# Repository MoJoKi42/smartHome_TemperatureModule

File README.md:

# smartHome_TemperatureModule
Temperature module for my smart home project based on a **ATmega324PB**. It can be powered by one/two 18650 BatteryCell or USB-C. If you use the battery, there is also a small PV charging circuit that makes battery replacement unnecessary.
Data communication works over the **433 Mhz band** with the RFM69 module soldered to the board.

Measurements can be taken every 8 seconds (or multiples thereof). There are also two sensor options on board. One option is the **SHT41** I2C digital temperature and humidity sensor from Sensirion. The other option is a standard 100R **NTC resistor** (in my case 44001RC) powered by a constant current source. The measurement is done with a differential ADC.

*keep in mind*: The firmware is still under development. Some changes need to be made to the data header for transmission.

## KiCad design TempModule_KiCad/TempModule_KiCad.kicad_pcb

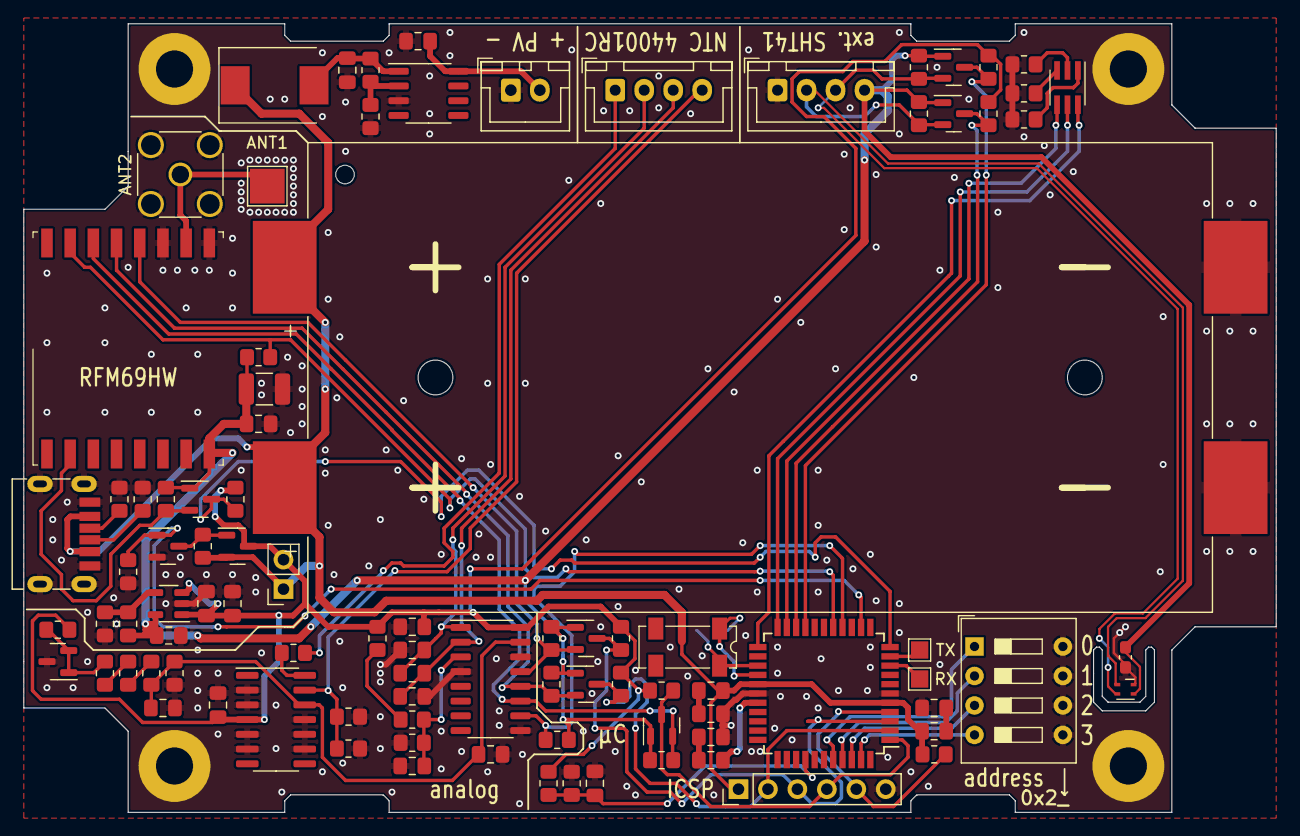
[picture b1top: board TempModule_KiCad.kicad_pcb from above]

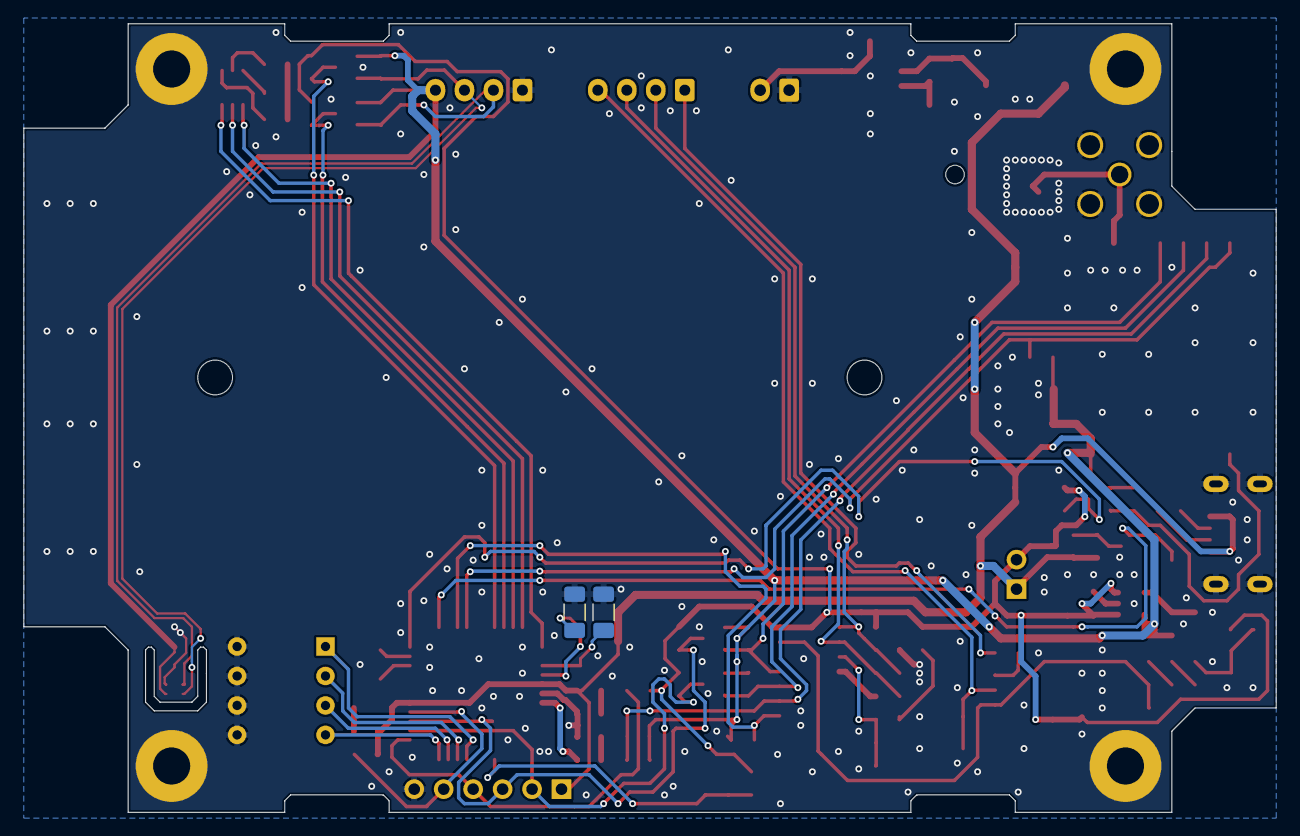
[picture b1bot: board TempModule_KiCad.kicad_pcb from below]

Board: 2 copper layers, 108.0 x 68.0 mm, 99 parts (2 on the bottom side), 58 nets.

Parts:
ANT1: ext. cable ANT; TestPoint_Pad_3.0x3.0mm
ANT2: SMA_connector; SMA_Wurth_60312002114503_Vertical
BATT1: 18650_SMD_Holder_2x
C1, C3, C5, C7, C8, C11, C12, C13, C15, C16, C17, C22, C23: 100n; C_0805_2012Metric_Pad1.18x1.45mm_HandSolder
C2: 10µ 16V; C_1210_3225Metric_Pad1.33x2.70mm_HandSolder
C4, C6: 2.2µ; C_0805_2012Metric_Pad1.18x1.45mm_HandSolder
C9, C14, C18, C19, C20, C21: 330n; C_0805_2012Metric_Pad1.18x1.45mm_HandSolder
C10: 100n; C_0603_1608Metric_Pad1.08x0.95mm_HandSolder
C24, C25: 15pF 1206; C_1206_3216Metric_Pad1.33x1.80mm_HandSolder
D1: VS-30BQ060; D_SMC
D2: ASMT-YTB2-0BB02; LED_Avago_PLCC6_3x2.8mm
J2: always_on_jumper; PinSocket_1x02_P2.54mm_Vertical
J3: 44001RC NTC; JST_XH_B4B-XH-A_1x04_P2.50mm_Vertical
J4: ICSP; PinHeader_1x06_P2.54mm_Vertical
J5: ext. SHT41; JST_XH_B4B-XH-A_1x04_P2.50mm_Vertical
J6: PV_Panel; JST_XH_B2B-XH-A_1x02_P2.50mm_Vertical
Q1: FDN306P; SOT-23
Q2: BSS138P; SOT-23
Q3, Q4, Q5, Q6, Q7, Q8: BSS138; SOT-23
R1, R4: 100k; R_0805_2012Metric_Pad1.20x1.40mm_HandSolder
R2, R8: 200R; R_0805_2012Metric_Pad1.20x1.40mm_HandSolder
R3, R5, R9, R10, R11, R12: 1k 0.5%; R_0805_2012Metric_Pad1.20x1.40mm_HandSolder
R6: 6.2k; R_0805_2012Metric_Pad1.20x1.40mm_HandSolder
R7, R16, R18, R19, R25, R26, R27, R28, R29, R30, R31, R32, R33, R34, R35, R36, R39: 10k; R_0805_2012Metric_Pad1.20x1.40mm_HandSolder
R13: 2k2; R_0805_2012Metric_Pad1.20x1.40mm_HandSolder
R14: 6k8; R_0805_2012Metric_Pad1.20x1.40mm_HandSolder
R15: 1k; R_0805_2012Metric_Pad1.20x1.40mm_HandSolder
R17: 47k; R_0805_2012Metric_Pad1.20x1.40mm_HandSolder
R20: 30k; R_0805_2012Metric_Pad1.20x1.40mm_HandSolder
R21: 7.5k; R_0805_2012Metric_Pad1.20x1.40mm_HandSolder
R22, R23, R24: 680R; R_0805_2012Metric_Pad1.20x1.40mm_HandSolder
R37, R38: 5.1k; R_0805_2012Metric_Pad1.20x1.40mm_HandSolder
SW1: SW_DIP_x04; SW_DIP_SPSTx04_Slide_9.78x12.34mm_W7.62mm_P2.54mm
TP2: TX; TestPoint_Pad_1.5x1.5mm
TP3: RX; TestPoint_Pad_1.5x1.5mm
U1: MCP6004; SO-14_3.9x8.65mm_P1.27mm
U2: RFM69HW; HOPERF_RFM69HW
U3: AP2210-ADJ; SOT-23-5
U4: TL432DBZ; SOT-23
U5: SHT41-AD1F-R2; Sensirion_DFN-4_1.5x1.5mm_P0.8mm_SHT4x_NoCentralPad
U6: LT1121CS8; SO-8_3.9x4.9mm_P1.27mm
U7: MCP3304; SO-16_3.9x9.9mm_P1.27mm
U8: ATmega324PB-A; TQFP-44_10x10mm_P0.8mm
U9: USB-C_6Pin_C2689837
U10, U11, U12, U13: Screw; Via_ScrewHole_3mm
Y1: Crystal_32.768_kHz; Crystal_SMD_SeikoEpson_MC306-4Pin_8.0x3.2mm

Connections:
+3.3V: C1.2, C2.1, C6.1, C10.2, J5.4, Q3.1 (G), Q4.1 (G), Q5.1 (G), Q6.1 (G), Q7.1 (G), Q8.1 (G), R6.1, R18.2, R19.2, R25.1, R27.1, R29.1, R31.1, R33.1, R35.1, U2.8 (3.3V), U3.5 (VOUT), U5.3 (VDD)
+BATT: BATT1.1 (+), C20.2, C21.2, D1.1 (K), J2.1, J4.1, Q1.2 (S), R1.1, R39.1, U8.5 (VCC), U8.27 (AVCC), U9.A9 (VBUS), U9.B9 (VBUS)
/A+: C11.2, C12.1, J3.2, U7.1 (CH0)
/A-: C12.2, C13.1, J3.3, U7.2 (CH1)
/SCL_3.3V: J5.3, Q7.2 (S), R33.2, U5.2 (SCL)
/SDA_3.3V: J5.2, Q8.2 (S), R35.2, U5.1 (SDA)
/U_Ref_0.625V: C7.1, C23.2, R11.2, R12.1, U1.12 (+), U7.15 (VREF)
/U_Ref_2.5V: R8.2, R9.1, U4.1 (REF), U4.2 (K)
/µC_unit/LED_B: D2.6 (AB), U8.23 (PC4)
/µC_unit/LED_G: D2.5 (AG), U8.22 (PC3)
/µC_unit/LED_R: D2.4 (AR), U8.21 (PC2)
/µC_unit/MISO: J4.2, Q4.3 (D), R28.1, U8.2 (PB6)
/µC_unit/MOSI: J4.4, Q5.3 (D), R30.1, U8.1 (PB5)
/µC_unit/RESET: J4.5, R39.2, U8.4 (~RESET)
/µC_unit/RFM_INT: Q6.3 (D), R32.1, U8.11 (PD2)
/µC_unit/RX: TP3.1, U8.9 (PD0)
/µC_unit/SCK: J4.3, Q3.3 (D), R26.1, U8.3 (PB7)
/µC_unit/TX: TP2.1, U8.10 (PD1)
CS_ADC_3.3V: R19.1, U7.10 (CS/SHDN), U8.15 (PD6)
CS_RFM_3.3V: R18.1, U2.15 (NSS), U8.16 (PD7)
GND: ANT2.2 (Ext), BATT1.2 (-), C1.1, C2.2, C3.1, C4.2, C5.2, C6.2, C7.2, C8.2, C9.1, C10.1, C11.1, C13.2, C14.1, C15.2, C16.1, C18.1, C19.1, C22.2, C23.1, C24.2, C25.2, J4.6, J5.1, J6.1, Q2.2 (S), R3.2, R4.2, R5.2, R7.2, R12.2, R15.2, R17.2, R21.2, R22.2, R23.2, R24.2, R37.2, R38.2, SW1.5, SW1.6, SW1.7, SW1.8, U1.2 (-), U1.3 (+), U1.5 (+), U1.6 (-), U1.9 (-), U1.10 (+), U1.11 (V-), U2.9 (GND), U2.11 (GND), U3.2 (GND), U4.3 (A), U5.4 (VSS), U6.3 (GND), U7.4 (CH3), U7.9 (DGND), U7.14 (AGND), U8.6 (GND), U8.28 (GND), U9.A12 (GND), U9.B12 (GND), U9.SHIELD, U10.1, U11.1, U12.1, U13.1
MISO_3.3V: Q4.2 (S), R27.2, U2.13 (MISO), U7.12 (DOUT)
MOSI_3.3V: Q5.2 (S), R29.2, U2.14 (MOSI), U7.11 (DIN)
unnamed: ANT1.1, ANT2.1 (In), U2.10 (ANA)
unnamed: C8.1, R14.2, R15.1, U7.3 (CH2)
unnamed: C9.2, J6.2, U6.8 (IN)
unnamed: C14.2, D1.2 (A), R16.1, U6.1 (OUT)
unnamed: C16.2, C17.1
unnamed: C17.2, U8.29 (PE4/AREF)
unnamed: C18.2, C20.1
unnamed: C19.2, C21.1
unnamed: C22.1, R20.2, R21.1, U8.37 (PA0)
unnamed: C24.1, U8.26 (PC7), Y1.1
unnamed: C25.1, U8.25 (PC6), Y1.4
unnamed: D2.1 (KB), R22.1
unnamed: D2.2 (KG), R23.1
unnamed: D2.3 (KR), R24.1
unnamed: J3.1, R2.2
unnamed: J3.4, R3.1, R5.1, U1.13 (-)
unnamed: Q1.1 (G), Q2.3 (D), R1.2
unnamed: R2.1, U1.14
unnamed: R6.2, R7.1, U3.4 (ADJ)
unnamed: R9.2, R10.1
unnamed: R10.2, R11.1
unnamed: R13.2, R14.1
unnamed: R16.2, R17.1, U6.2 (ADJ)
unnamed: R37.1, U9.B5 (VCONN)
unnamed: R38.1, U9.A5 (CC)
unnamed: SW1.1, U8.40 (PB0)
unnamed: SW1.2, U8.41 (PB1)
unnamed: SW1.3, U8.42 (PB2)
unnamed: SW1.4, U8.43 (PB3)
Power_on: Q2.1 (G), R4.1, U8.13 (PD4)
RFM_INT_3.3V: Q6.2 (S), R31.2, U2.2 (DIO0)
SCK_3.3V: Q3.2 (S), R25.2, U2.12 (SCK), U7.13 (CLK)
SCL: Q7.3 (D), R34.1, U8.19 (PC0)
SDA: Q8.3 (D), R36.1, U8.20 (PC1)
VCC: C3.2, C4.1, C5.1, C15.1, J2.2, Q1.3 (D), R8.1, R13.1, R20.1, R26.2, R28.2, R30.2, R32.2, R34.2, R36.2, U1.4 (V+), U3.1 (VIN), U3.3 (EN), U7.16 (VDD)

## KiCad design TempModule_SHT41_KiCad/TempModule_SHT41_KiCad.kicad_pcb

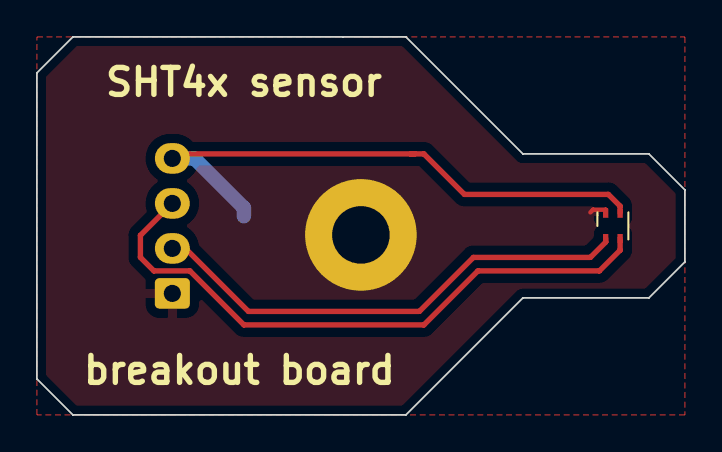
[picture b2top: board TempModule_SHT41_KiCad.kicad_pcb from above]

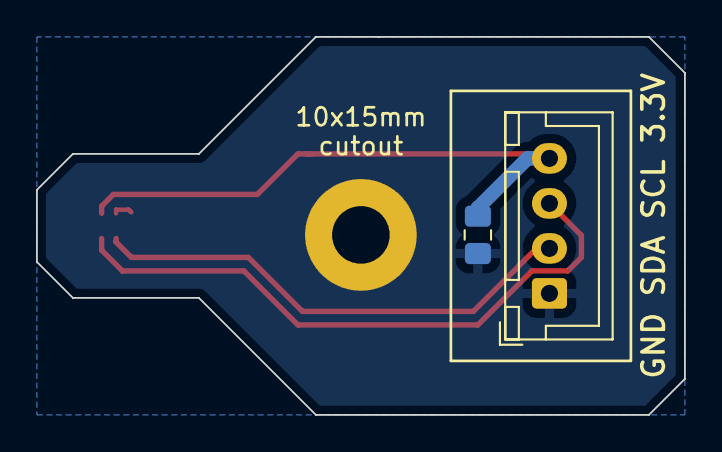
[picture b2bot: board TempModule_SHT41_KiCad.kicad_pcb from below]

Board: 2 copper layers, 36.0 x 21.0 mm, 4 parts (2 on the bottom side), 4 nets.

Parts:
C1: 100n; C_0805_2012Metric_Pad1.18x1.45mm_HandSolder
J1: ext. SHT41; JST_XH_B4B-XH-A_1x04_P2.50mm_Vertical
U1: Screw; Via_ScrewHole_3mm
U2: SHT41-AD1F-R2; Sensirion_DFN-4_1.5x1.5mm_P0.8mm_SHT4x_NoCentralPad

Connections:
+3.3V: C1.2, J1.4, U2.3 (VDD)
/SCL_3.3V: J1.3, U2.2 (SCL)
/SDA_3.3V: J1.2, U2.1 (SDA)
GND: C1.1, J1.1, U1.1, U2.4 (VSS)

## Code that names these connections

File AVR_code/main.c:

#include <avr/io.h>
#include <avr/interrupt.h>
#include <avr/sleep.h>
#include <util/delay.h>
#include <stdio.h>
#include <stdlib.h>
#include <math.h>
#include <time.h>
#include "radio.h"
#include "twi.h"
#include "RFM69.h"
#include "RFM69registers.h"
#include "sht4x.h"
#include "adc.h"

// Commands :
//
// -> Compile
// make all
//
// -> Flashing
// avrdude -p m324pb -c usbasp -e -U flash:w:main.hex
// avrdude -p m324pb -c dragon_isp -e -U flash:w:main.hex
//
// -> Write Fuses
// avrdude -c usbasp -p m324pb -U lfuse:w:0x42:m -U hfuse:w:0xD9:m -U efuse:w:0xFF:m
// avrdude -c dragon_isp -p m324pb -U lfuse:w:0x42:m -U hfuse:w:0xD9:m -U efuse:w:0xFF:m
//
// -> VS Code Include Pfad
// "/usr/lib/avr/include"
//

// Port definitions
#define LED_R_off    PORTC &= ~(1<<PC2)
#define LED_R_on     PORTC |=  (1<<PC2)
#define LED_G_off    PORTC &= ~(1<<PC3)
#define LED_G_on     PORTC |=  (1<<PC3)
#define LED_B_off    PORTC &= ~(1<<PC4)
#define LED_B_on     PORTC |=  (1<<PC4)

#define PowerON      PORTD |=  (1<<PD4)
#define PowerOFF     PORTD &= ~(1<<PD4)

#define CS_ADC_en    DDRD |=  (1<<PD6)
#define CS_ADC_dis   DDRD &=  ~(1<<PD6)
#define CS_RFM_en    DDRD |=  (1<<PD7)  // see "RFM69.h" on line 39
#define CS_RFM_dis   DDRD &=  ~(1<<PD7) // see "RFM69.h" on line 39


// Prototypes
void sleep_init(void);
void sleep_start(uint16_t duration);


// RFM69 definitions
#define MaxRetries          1
#define MaxRetryWaitTime    250  // max 250ms  
#define NETWORKID           33
const char EncryptKey[16] = "1234567812345678";
uint8_t    deviceID       = 0x20;
uint8_t    baseID         = 0x01;   // ID of base station



// ToDo:
// - Datenheader anpassen
// - Schauen welche Delays verkürzt werden können!



int main(void) {

    // Outputs
    DDRC  |= (1<<PC2)|(1<<PC3)|(1<<PC4);            // Output LEDs
    DDRD  |= (1<<PD4);                              // Output PowerON Pin
    PORTB |= (1<<PB0)|(1<<PB1)|(1<<PB2)|(1<<PB3);   // Enable Address PullUps
    CS_ADC_dis;
    CS_RFM_dis;
    
    PowerON;
    _delay_ms(200);
    
    // get DeviceID 
    deviceID |= (~PINB & 0x0F);
    if (deviceID == 0x20) {
        while(1) {
            LED_R_on;       // address 0x20 not allowed!
            _delay_ms(200);
            LED_R_off;
            _delay_ms(200);
        }
    }
    
    // init Sleep
    sleep_init();
    
    
    while (1) {
        
        // enable LED
        LED_B_on;
        
        // init RFM69
        rfm69_init(433, deviceID, NETWORKID);
        setHighPower(1);    // if model number rfm69hw
        setPowerLevel(30);  // 0-31; 5dBm to 20 dBm
        encrypt(EncryptKey);
        
        // init SHT41
        sht4x_init_twi();
        
        // measurement SHT41
        sht4x_send_cmd(0xFD);
        _delay_ms(200);
        uint8_t data[6];
        float temperature;
        float humidity;
        if (sht4x_read_data(data)) {
            temperature =  0.0;   // got invalid data
            humidity = 0.0;       // got invalid data
        } else {
            temperature =  sht4x_get_temperature_from_data(data);
            humidity =     sht4x_get_humidity_from_data(data);
        }
        
        // measurement batteryVoltage
        adc_init();
        float batteryVoltage = adc_read_avg(0, 10);
        batteryVoltage = batteryVoltage * (5.0 * 1.1 / 1023.0);
        
        
        // generate json string
        char str[200];
        sprintf(str, "{\"deviceID_hex\":%x,\"uptime\":%d,\"batteryVoltage\":%0.3f,\"temperature\":%0.2f,\"humidity\":%0.2f}",
                         deviceID,           0,            batteryVoltage,          temperature,          humidity);
        
        
        // get number of single packets
        uint16_t data_length = strlen(str);
        uint8_t MAX_DATA_LEN = RF69_MAX_DATA_LEN - RADIO_HEADER_LEN;
        uint8_t packet_cnt = data_length/MAX_DATA_LEN;
        if (data_length % MAX_DATA_LEN)
            packet_cnt++;
        
        // send packets
        uint8_t successful_transmitted = 1;
        for (int packet=0; packet < packet_cnt; packet++) {
            
            // calculate packet length
            uint8_t packet_lenght;
            if (packet == packet_cnt-1 && data_length % MAX_DATA_LEN) {
                packet_lenght = data_length % MAX_DATA_LEN;
            } else {
                packet_lenght = MAX_DATA_LEN;
            }
            
            // add data header
            uint8_t buffer[RF69_MAX_DATA_LEN];
            uint8_t buffer_len = radio_generate_header(buffer, str + (packet*MAX_DATA_LEN), packet_lenght, packet, packet_cnt, RADIO_DATATYPE_MQTT_JSON, deviceID, baseID);
        
            // send data
            uint8_t statusACK = 0;
            uint8_t retry = 0; uint8_t timeRetry = 0;
            while (retry < MaxRetries) {
                
                // send
                send(baseID, buffer, buffer_len, 1);
                
                // check ACK + wait
                timeRetry = 0;
                while (timeRetry < MaxRetryWaitTime) {
                    statusACK = ACKReceived(baseID);
                    if (statusACK) { break; }
                    _delay_ms(1);
                    timeRetry++;
                }
                
                // abort next retry when ACK received
                if (statusACK) { break; }
                retry++;
            }
            
            // reset "successful_transmitted"-variable when one ACK is missing
            if (!statusACK)
                successful_transmitted = 0;
        }
        
        // power off
        PowerOFF;
        
        // show ACK/NACK with LEDs
        LED_B_off;
        if (successful_transmitted) {
            LED_G_on;
        } else {
            LED_R_on;
        }
        _delay_ms(100);
        LED_R_off;
        LED_G_off;
        
        // sleep
        sleep_start(8);
        PowerON;
        _delay_ms(100);
    }
    
}


////////////////////////////////////////////////////////////////////////////////////////////
// sleep functions
////////////////////////////////////////////////////////////////////////////////////////////

// init sleep registers
void sleep_init(void) {
    
    ASSR = (1<<AS2);                                // select asynchronous operation of Timer2
    TCCR2A = 0x00;                                  // Normal mode
    TCCR2B = (1<<CS22) | (1<<CS21) | (1<<CS20) ;    // Prescaler = 1024
    TIMSK2 = (1<<TOIE2);                            // Timer0 overflow interrup enable
    TCNT2 =  0;                                     // Preload Value
    
    while((ASSR & (1<<OCR2AUB)) || (ASSR & (1<<OCR2BUB)));  // wait
    while((ASSR & (1<<TCR2AUB)) || (ASSR & (1<<TCR2BUB)));  // wait
    while((ASSR & (1<<TCN2UB)));                            // wait
}

// Timer2 overflow Interrupt (sleep functions)
ISR(TIMER2_OVF_vect) { }

// go sleeping function
// duration = 8...2048 seconds (in 8 seconds steps)
void sleep_start(uint16_t duration) {
    
    // set sleep duration
    uint8_t sleep_counter = 0;
    if (duration >= 2048) {
        sleep_counter = 255;
    } else {
        sleep_counter = duration / 8;
    }
    
    sei();                                  // enable interrups
    for (int i=0; i<sleep_counter; i++) {
        set_sleep_mode(SLEEP_MODE_PWR_SAVE);    // set sleep mode
        sleep_mode();                           // go sleeping
    }
    cli();                                  // disable intrrups
}

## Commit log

2023-11-21 init
